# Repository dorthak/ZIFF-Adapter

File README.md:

# ZIFF-Adapter
Adapter for mounting a wide ZIFF socket on a breadboard.

This is an adapter designed to mount a wide ZIFF socket with 0.1" spacing between pins and 0.6" spacing between rows (such as this one: https://www.amazon.com/dp/B0BS9LB2LM) on a standard breadboard.  Without it, the socket's very short pins tend to pop out of the breadboard.  This adapter also allows one to install extra long pins, elevating the adapter and socket above the breadboard and allowing wires to be run under it.  

Kicad 8.0 and gerber files are provided.  You should be able to order the PCBs from any board house.

You will need a ZIFF socket of the appropriate size and some 0.1" header pins.  Be sure to solder the header pins first!

Some photos of the adapter in use:

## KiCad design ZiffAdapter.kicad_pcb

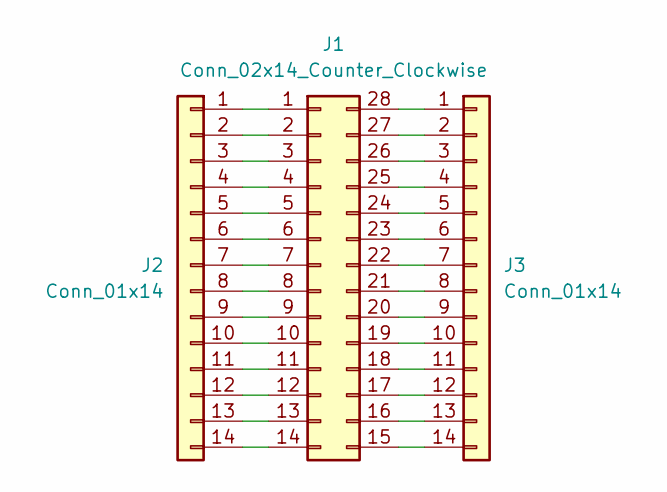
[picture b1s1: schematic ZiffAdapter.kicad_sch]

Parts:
J1: Conn_02x14_Counter_Clockwise; ZIFF Socket - DIP-28 - 15.24mm x 2.54mm
J2, J3: Conn_01x14; PinHeader_1x14_P2.54mm_Vertical

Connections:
unnamed: J1.1, J2.1
unnamed: J1.2, J2.2
unnamed: J1.3, J2.3
unnamed: J1.4, J2.4
unnamed: J1.5, J2.5
unnamed: J1.6, J2.6
unnamed: J1.7, J2.7
unnamed: J1.8, J2.8
unnamed: J1.9, J2.9
unnamed: J1.10, J2.10
unnamed: J1.11, J2.11
unnamed: J1.12, J2.12
unnamed: J1.13, J2.13
unnamed: J1.14, J2.14
unnamed: J1.15, J3.14
unnamed: J1.16, J3.13
unnamed: J1.17, J3.12
unnamed: J1.18, J3.11
unnamed: J1.19, J3.10
unnamed: J1.20, J3.9
unnamed: J1.21, J3.8
unnamed: J1.22, J3.7
unnamed: J1.23, J3.6
unnamed: J1.24, J3.5
unnamed: J1.25, J3.4
unnamed: J1.26, J3.3
unnamed: J1.27, J3.2
unnamed: J1.28, J3.1

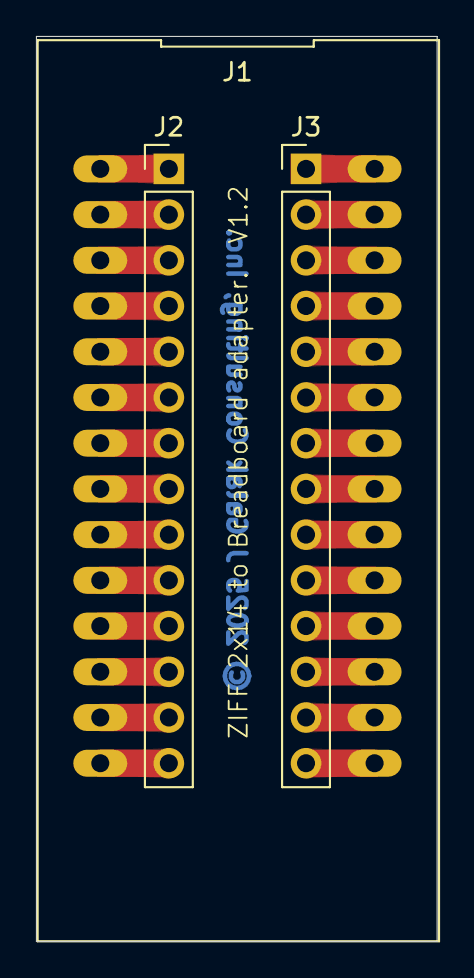
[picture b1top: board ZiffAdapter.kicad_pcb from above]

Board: 2 copper layers, 22.3 x 50.3 mm, 3 parts (0 on the bottom side), 28 nets.

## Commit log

2025-10-03 Added images
2025-10-03 Deleted extraneous file

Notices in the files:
ZiffAdapter.kicad_pcb:
© 2025 J Galak Consulting, Inc.
